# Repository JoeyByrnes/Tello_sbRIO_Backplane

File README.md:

# Tello_sbRIO_Backplane
Hardware Design Files for Tello sbRIO Backplane. For Connecting 10 BiSS-C encoders and 10 AMC drivers to sbRIO.
<br>
<br>
Note: This PCB was not used. I designed this before joining RoboDesign Lab. After joining, I changed the Tello electronics to use a linux computer and MIT mini-cheetah style drivers instead of the sbRIO and AMC drivers.
<br>
<br>
<p>
  
  <br>&nbsp;<br>
  
</p>

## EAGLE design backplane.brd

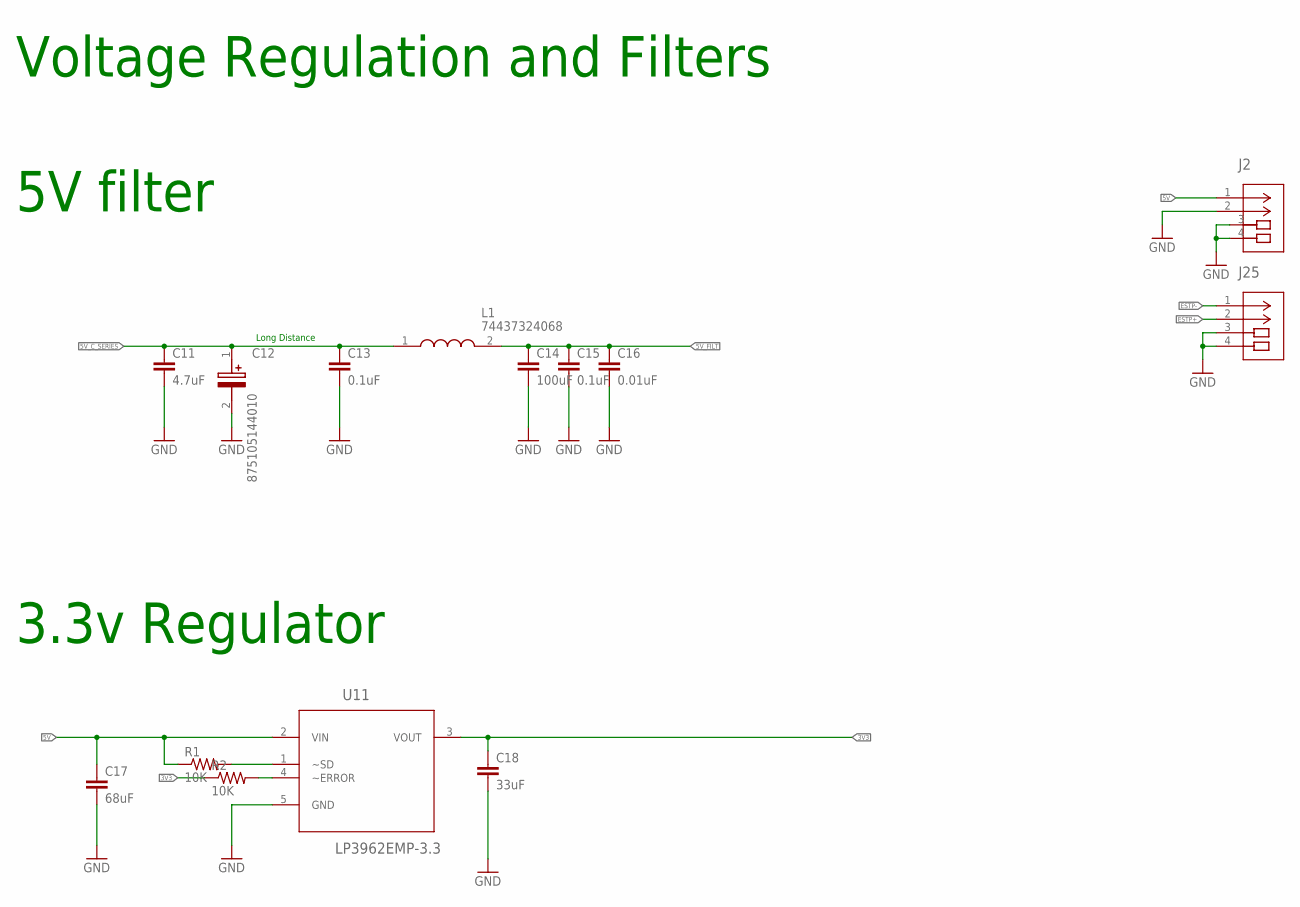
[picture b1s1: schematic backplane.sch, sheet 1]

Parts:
C11: 4.7uF; C0603
C12: 875105144010; CAPAE660X580N
C13, C15: 0.1uF; C0603
C14: 100uF; C1206
C16: 0.01uF; C0603
C17: 68uF; C1206
C18: 33uF; C1206
J2: 1054301102; CON_1054301102_MOL
J25: 5055670271; CON_5055670271
L1: 74437324068; WE-LHMI_402048
R1, R2: 10K; R0603
U11: LP3962EMP-3.3; SOT150P696X180-5N

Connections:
3V3: C18.1, R2.1, U11.3 (VOUT); also elsewhere on the board
5V: C17.1, J2.1, R1.1, U11.2 (VIN); also elsewhere on the board
5V_C_SERIES: C11.1, C12.1 (+), C13.1, L1.1; also elsewhere on the board
5V_FILT: C14.1, C15.1, C16.1, L1.2; also elsewhere on the board
ESTP+: J25.2; also elsewhere on the board
ESTP-: J25.1; also elsewhere on the board
GND: C11.2, C12.2 (-), C13.2, C14.2, C15.2, C16.2, C17.2, C18.2, J2.2, J2.3, J2.4, J25.3, J25.4, U11.5 (GND); also elsewhere on the board
unnamed: R1.2, U11.1 (~SD)
unnamed: R2.2, U11.4 (~ERROR)

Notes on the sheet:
Voltage Regulation and Filters
5V filter
3.3v Regulator
Long Distance

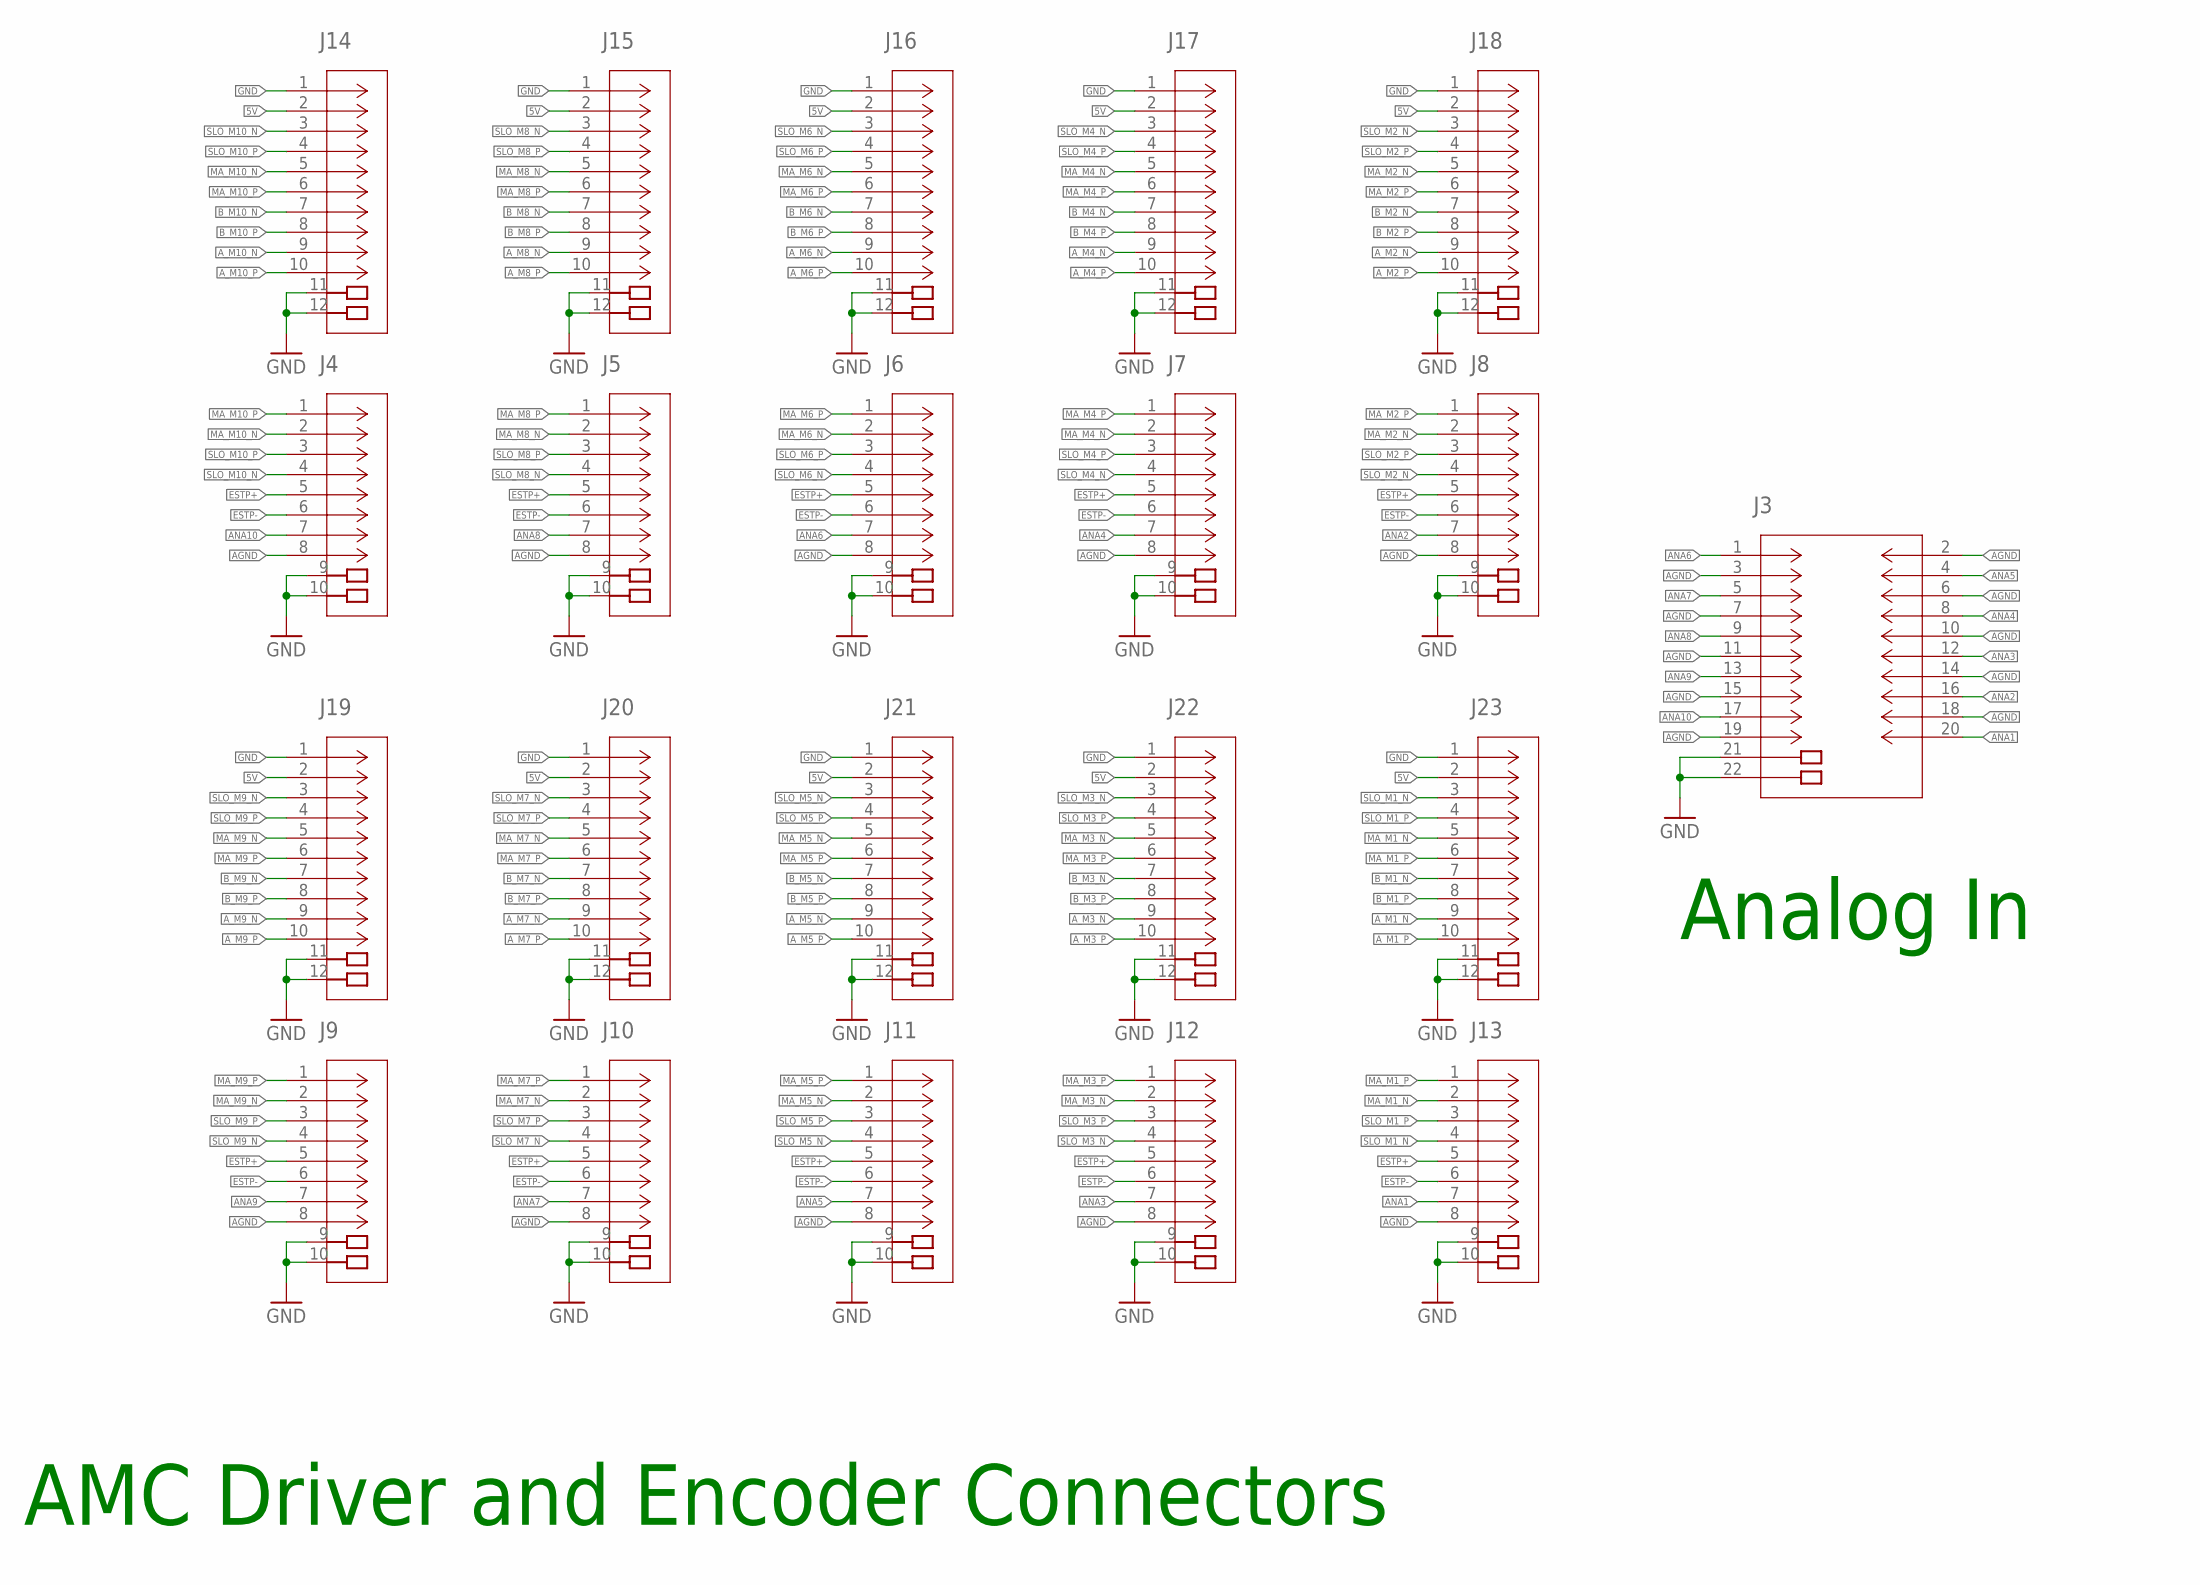
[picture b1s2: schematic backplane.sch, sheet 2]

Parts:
J3: 5011902017; CON_5011902017
J4, J5, J6, J7, J8, J9, J10, J11, J12, J13: 5013310807; CON_5013310807
J14, J15, J16, J17, J18, J19, J20, J21, J22, J23: 5013311007; CON_5013311007

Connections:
5V: J14.2, J15.2, J16.2, J17.2, J18.2, J19.2, J20.2, J21.2, J22.2, J23.2; also elsewhere on the board
AGND: J3.2, J3.3, J3.6, J3.7, J3.10, J3.11, J3.14, J3.15, J3.18, J3.19, J4.8, J5.8, J6.8, J7.8, J8.8, J9.8, J10.8, J11.8, J12.8, J13.8
ANA1: J3.20, J13.7
ANA2: J3.16, J8.7
ANA3: J3.12, J12.7
ANA4: J3.8, J7.7
ANA5: J3.4, J11.7
ANA6: J3.1, J6.7
ANA7: J3.5, J10.7
ANA8: J3.9, J5.7
ANA9: J3.13, J9.7
ANA10: J3.17, J4.7
A_M1_N: J23.9; also elsewhere on the board
A_M1_P: J23.10; also elsewhere on the board
A_M2_N: J18.9; also elsewhere on the board
A_M2_P: J18.10; also elsewhere on the board
A_M3_N: J22.9; also elsewhere on the board
A_M3_P: J22.10; also elsewhere on the board
A_M4_N: J17.9; also elsewhere on the board
A_M4_P: J17.10; also elsewhere on the board
A_M5_N: J21.9; also elsewhere on the board
A_M5_P: J21.10; also elsewhere on the board
A_M6_N: J16.9; also elsewhere on the board
A_M6_P: J16.10; also elsewhere on the board
A_M7_N: J20.9; also elsewhere on the board
A_M7_P: J20.10; also elsewhere on the board
A_M8_N: J15.9; also elsewhere on the board
A_M8_P: J15.10; also elsewhere on the board
A_M9_N: J19.9; also elsewhere on the board
A_M9_P: J19.10; also elsewhere on the board
A_M10_N: J14.9; also elsewhere on the board
A_M10_P: J14.10; also elsewhere on the board
B_M1_N: J23.7; also elsewhere on the board
B_M1_P: J23.8; also elsewhere on the board
B_M2_N: J18.7; also elsewhere on the board
B_M2_P: J18.8; also elsewhere on the board
B_M3_N: J22.7; also elsewhere on the board
B_M3_P: J22.8; also elsewhere on the board
B_M4_N: J17.7; also elsewhere on the board
B_M4_P: J17.8; also elsewhere on the board
B_M5_N: J21.7; also elsewhere on the board
B_M5_P: J21.8; also elsewhere on the board
B_M6_N: J16.7; also elsewhere on the board
B_M6_P: J16.8; also elsewhere on the board
B_M7_N: J20.7; also elsewhere on the board
B_M7_P: J20.8; also elsewhere on the board
B_M8_N: J15.7; also elsewhere on the board
B_M8_P: J15.8; also elsewhere on the board
B_M9_N: J19.7; also elsewhere on the board
B_M9_P: J19.8; also elsewhere on the board
B_M10_N: J14.7; also elsewhere on the board
B_M10_P: J14.8; also elsewhere on the board
ESTP+: J4.5, J5.5, J6.5, J7.5, J8.5, J9.5, J10.5, J11.5, J12.5, J13.5; also elsewhere on the board
ESTP-: J4.6, J5.6, J6.6, J7.6, J8.6, J9.6, J10.6, J11.6, J12.6, J13.6; also elsewhere on the board
GND: J3.21, J3.22, J4.9, J4.10, J5.9, J5.10, J6.9, J6.10, J7.9, J7.10, J8.9, J8.10, J9.9, J9.10, J10.9, J10.10, J11.9, J11.10, J12.9, J12.10, J13.9, J13.10, J14.1, J14.11, J14.12, J15.1, J15.11, J15.12, J16.1, J16.11, J16.12, J17.1, J17.11, J17.12, J18.1, J18.11, J18.12, J19.1, J19.11, J19.12, J20.1, J20.11, J20.12, J21.1, J21.11, J21.12, J22.1, J22.11, J22.12, J23.1, J23.11, J23.12; also elsewhere on the board
MA_M1_N: J13.2, J23.5; also elsewhere on the board
MA_M1_P: J13.1, J23.6; also elsewhere on the board
MA_M2_N: J8.2, J18.5; also elsewhere on the board
MA_M2_P: J8.1, J18.6; also elsewhere on the board
MA_M3_N: J12.2, J22.5; also elsewhere on the board
MA_M3_P: J12.1, J22.6; also elsewhere on the board
MA_M4_N: J7.2, J17.5; also elsewhere on the board
MA_M4_P: J7.1, J17.6; also elsewhere on the board
MA_M5_N: J11.2, J21.5; also elsewhere on the board
MA_M5_P: J11.1, J21.6; also elsewhere on the board
MA_M6_N: J6.2, J16.5; also elsewhere on the board
MA_M6_P: J6.1, J16.6; also elsewhere on the board
MA_M7_N: J10.2, J20.5; also elsewhere on the board
MA_M7_P: J10.1, J20.6; also elsewhere on the board
MA_M8_N: J5.2, J15.5; also elsewhere on the board
MA_M8_P: J5.1, J15.6; also elsewhere on the board
MA_M9_N: J9.2, J19.5; also elsewhere on the board
MA_M9_P: J9.1, J19.6; also elsewhere on the board
MA_M10_N: J4.2, J14.5; also elsewhere on the board
MA_M10_P: J4.1, J14.6; also elsewhere on the board
SLO_M1_N: J13.4, J23.3; also elsewhere on the board
SLO_M1_P: J13.3, J23.4; also elsewhere on the board
SLO_M2_N: J8.4, J18.3; also elsewhere on the board
SLO_M2_P: J8.3, J18.4; also elsewhere on the board
SLO_M3_N: J12.4, J22.3; also elsewhere on the board
SLO_M3_P: J12.3, J22.4; also elsewhere on the board
SLO_M4_N: J7.4, J17.3; also elsewhere on the board
SLO_M4_P: J7.3, J17.4; also elsewhere on the board
SLO_M5_N: J11.4, J21.3; also elsewhere on the board
SLO_M5_P: J11.3, J21.4; also elsewhere on the board
SLO_M6_N: J6.4, J16.3; also elsewhere on the board
SLO_M6_P: J6.3, J16.4; also elsewhere on the board
SLO_M7_N: J10.4, J20.3; also elsewhere on the board
SLO_M7_P: J10.3, J20.4; also elsewhere on the board
SLO_M8_N: J5.4, J15.3; also elsewhere on the board
SLO_M8_P: J5.3, J15.4; also elsewhere on the board
SLO_M9_N: J9.4, J19.3; also elsewhere on the board
SLO_M9_P: J9.3, J19.4; also elsewhere on the board
SLO_M10_N: J4.4, J14.3; also elsewhere on the board
SLO_M10_P: J4.3, J14.4; also elsewhere on the board

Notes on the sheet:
AMC Driver and Encoder Connectors
Analog In

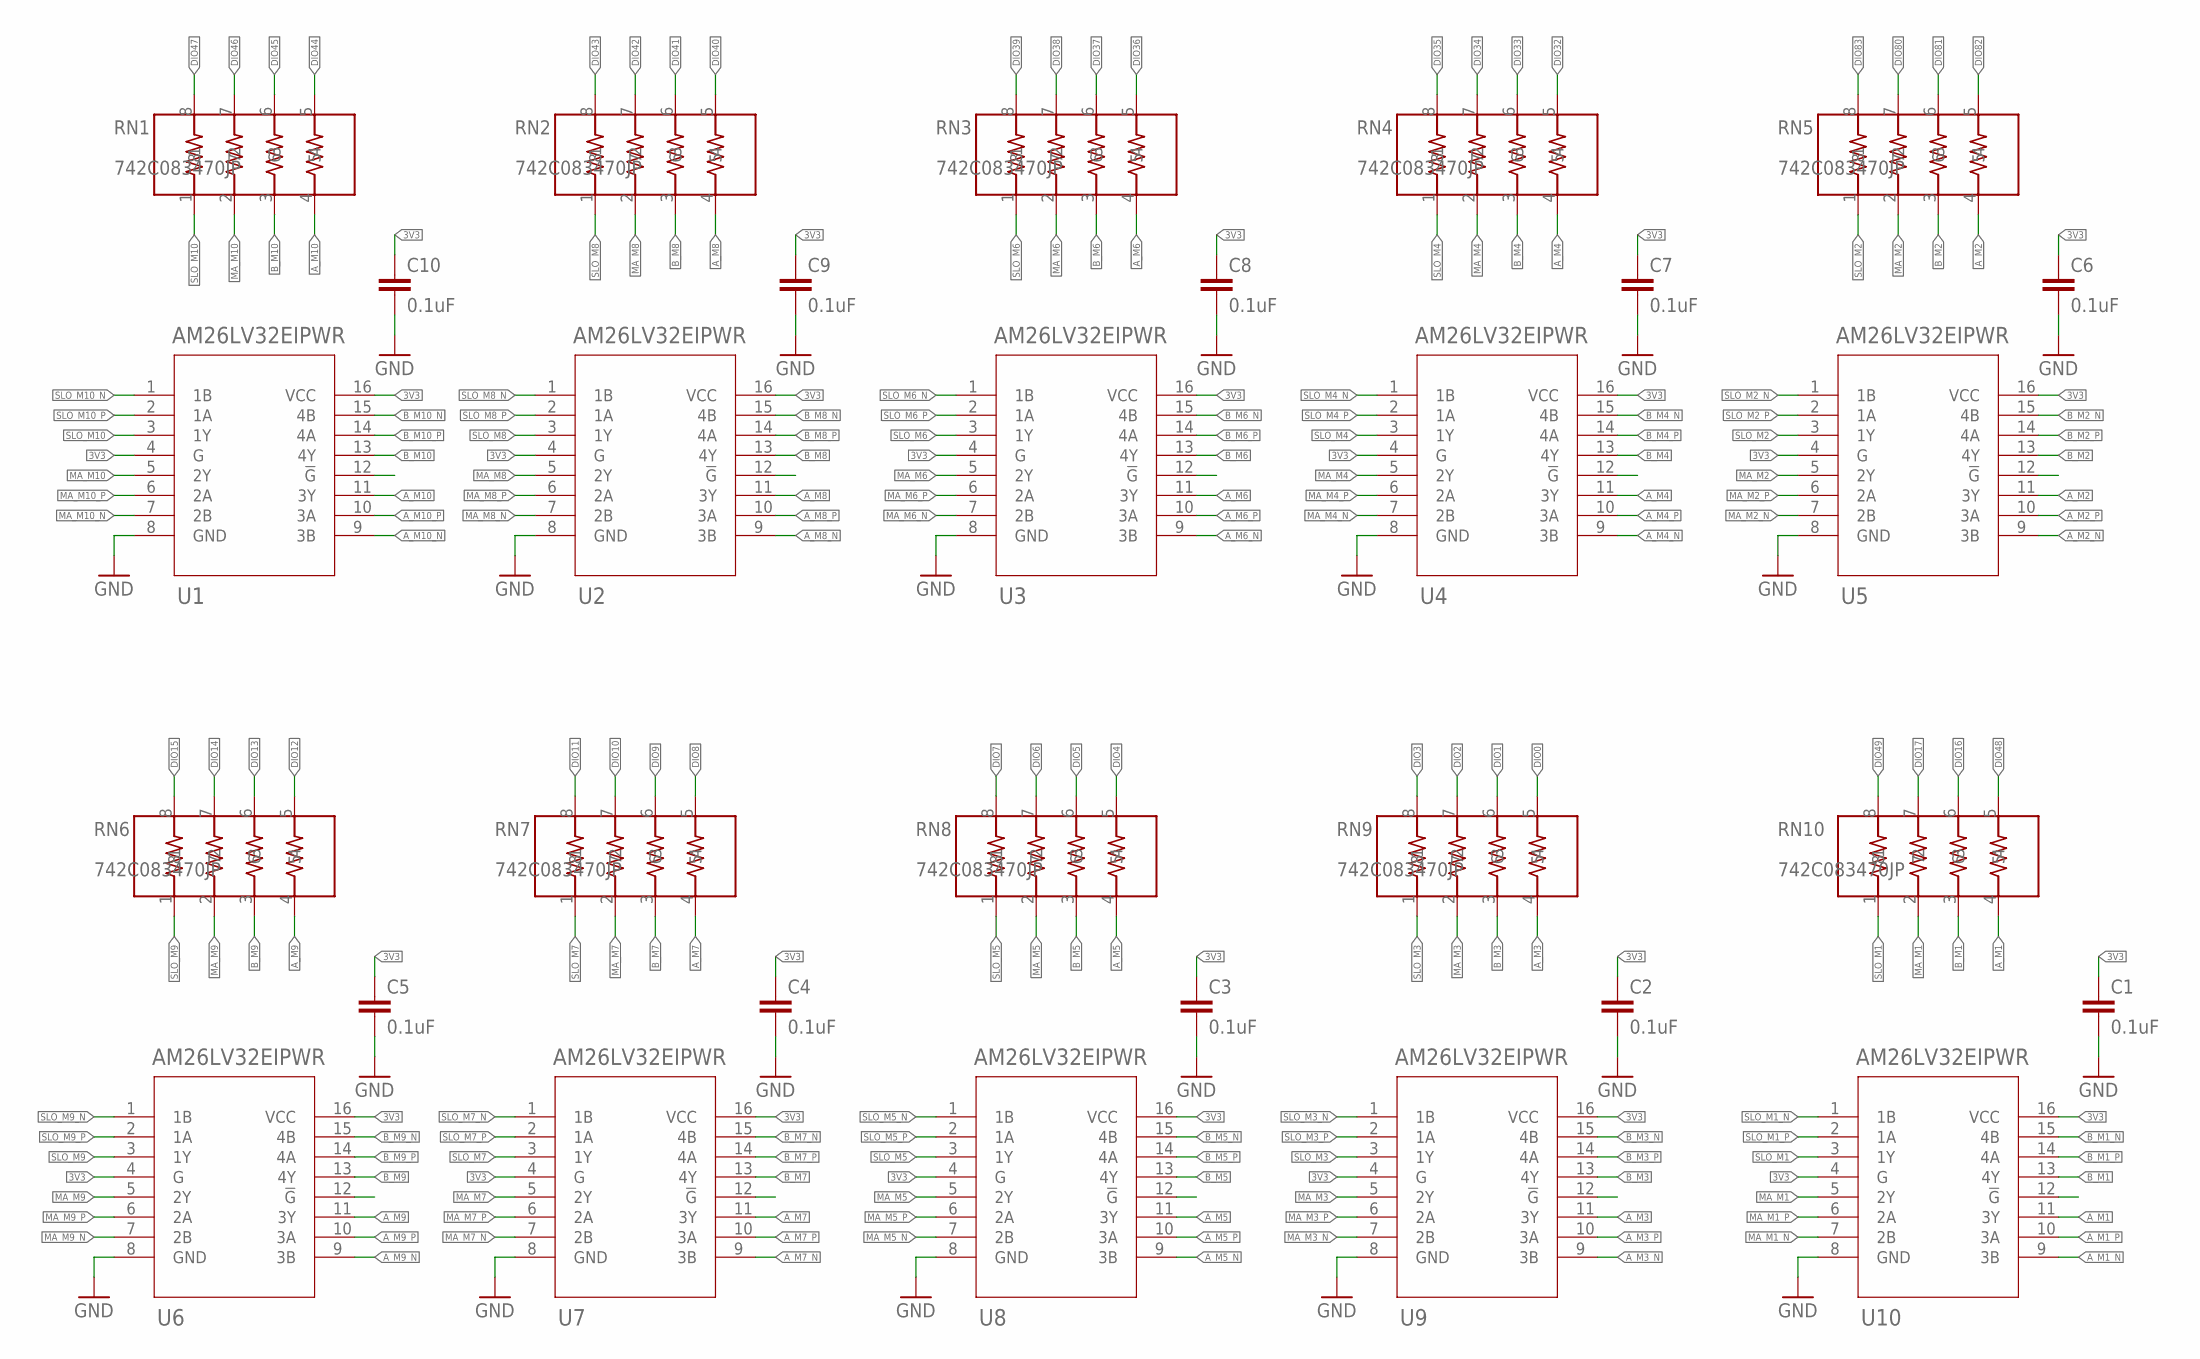
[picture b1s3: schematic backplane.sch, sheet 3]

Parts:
C1, C2, C3, C4, C5, C6, C7, C8, C9, C10: 0.1uF; C0603
RN1, RN2, RN3, RN4, RN5, RN6, RN7, RN8, RN9, RN10: 742C083470JP; RESCAV80P320X160X70-8N
U1, U2, U3, U4, U5, U6, U7, U8, U9, U10: AM26LV32EIPWR; PW16

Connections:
3V3: C1.1, C2.1, C3.1, C4.1, C5.1, C6.1, C7.1, C8.1, C9.1, C10.1, U1.4 (G), U1.16 (VCC), U2.4 (G), U2.16 (VCC), U3.4 (G), U3.16 (VCC), U4.4 (G), U4.16 (VCC), U5.4 (G), U5.16 (VCC), U6.4 (G), U6.16 (VCC), U7.4 (G), U7.16 (VCC), U8.4 (G), U8.16 (VCC), U9.4 (G), U9.16 (VCC), U10.4 (G), U10.16 (VCC); also elsewhere on the board
A_M1: RN10.4, U10.11 (3Y)
A_M1_N: U10.9 (3B); also elsewhere on the board
A_M1_P: U10.10 (3A); also elsewhere on the board
A_M2: RN5.4, U5.11 (3Y)
A_M2_N: U5.9 (3B); also elsewhere on the board
A_M2_P: U5.10 (3A); also elsewhere on the board
A_M3: RN9.4, U9.11 (3Y)
A_M3_N: U9.9 (3B); also elsewhere on the board
A_M3_P: U9.10 (3A); also elsewhere on the board
A_M4: RN4.4, U4.11 (3Y)
A_M4_N: U4.9 (3B); also elsewhere on the board
A_M4_P: U4.10 (3A); also elsewhere on the board
A_M5: RN8.4, U8.11 (3Y)
A_M5_N: U8.9 (3B); also elsewhere on the board
A_M5_P: U8.10 (3A); also elsewhere on the board
A_M6: RN3.4, U3.11 (3Y)
A_M6_N: U3.9 (3B); also elsewhere on the board
A_M6_P: U3.10 (3A); also elsewhere on the board
A_M7: RN7.4, U7.11 (3Y)
A_M7_N: U7.9 (3B); also elsewhere on the board
A_M7_P: U7.10 (3A); also elsewhere on the board
A_M8: RN2.4, U2.11 (3Y)
A_M8_N: U2.9 (3B); also elsewhere on the board
A_M8_P: U2.10 (3A); also elsewhere on the board
A_M9: RN6.4, U6.11 (3Y)
A_M9_N: U6.9 (3B); also elsewhere on the board
A_M9_P: U6.10 (3A); also elsewhere on the board
A_M10: RN1.4, U1.11 (3Y)
A_M10_N: U1.9 (3B); also elsewhere on the board
A_M10_P: U1.10 (3A); also elsewhere on the board
B_M1: RN10.3, U10.13 (4Y)
B_M1_N: U10.15 (4B); also elsewhere on the board
B_M1_P: U10.14 (4A); also elsewhere on the board
B_M2: RN5.3, U5.13 (4Y)
B_M2_N: U5.15 (4B); also elsewhere on the board
B_M2_P: U5.14 (4A); also elsewhere on the board
B_M3: RN9.3, U9.13 (4Y)
B_M3_N: U9.15 (4B); also elsewhere on the board
B_M3_P: U9.14 (4A); also elsewhere on the board
B_M4: RN4.3, U4.13 (4Y)
B_M4_N: U4.15 (4B); also elsewhere on the board
B_M4_P: U4.14 (4A); also elsewhere on the board
B_M5: RN8.3, U8.13 (4Y)
B_M5_N: U8.15 (4B); also elsewhere on the board
B_M5_P: U8.14 (4A); also elsewhere on the board
B_M6: RN3.3, U3.13 (4Y)
B_M6_N: U3.15 (4B); also elsewhere on the board
B_M6_P: U3.14 (4A); also elsewhere on the board
B_M7: RN7.3, U7.13 (4Y)
B_M7_N: U7.15 (4B); also elsewhere on the board
B_M7_P: U7.14 (4A); also elsewhere on the board
B_M8: RN2.3, U2.13 (4Y)
B_M8_N: U2.15 (4B); also elsewhere on the board
B_M8_P: U2.14 (4A); also elsewhere on the board
B_M9: RN6.3, U6.13 (4Y)
B_M9_N: U6.15 (4B); also elsewhere on the board
B_M9_P: U6.14 (4A); also elsewhere on the board
B_M10: RN1.3, U1.13 (4Y)
B_M10_N: U1.15 (4B); also elsewhere on the board
B_M10_P: U1.14 (4A); also elsewhere on the board
DIO0: RN9.5; also elsewhere on the board
DIO1: RN9.6; also elsewhere on the board
DIO2: RN9.7; also elsewhere on the board
DIO3: RN9.8; also elsewhere on the board
DIO4: RN8.5; also elsewhere on the board
DIO5: RN8.6; also elsewhere on the board
DIO6: RN8.7; also elsewhere on the board
DIO7: RN8.8; also elsewhere on the board
DIO8: RN7.5; also elsewhere on the board
DIO9: RN7.6; also elsewhere on the board
DIO10: RN7.7; also elsewhere on the board
DIO11: RN7.8; also elsewhere on the board
DIO12: RN6.5; also elsewhere on the board
DIO13: RN6.6; also elsewhere on the board
DIO14: RN6.7; also elsewhere on the board
DIO15: RN6.8; also elsewhere on the board
DIO16: RN10.6; also elsewhere on the board
DIO17: RN10.7; also elsewhere on the board
DIO32: RN4.5; also elsewhere on the board
DIO33: RN4.6; also elsewhere on the board
DIO34: RN4.7; also elsewhere on the board
DIO35: RN4.8; also elsewhere on the board
DIO36: RN3.5; also elsewhere on the board
DIO37: RN3.6; also elsewhere on the board
DIO38: RN3.7; also elsewhere on the board
DIO39: RN3.8; also elsewhere on the board
DIO40: RN2.5; also elsewhere on the board
DIO41: RN2.6; also elsewhere on the board
DIO42: RN2.7; also elsewhere on the board
DIO43: RN2.8; also elsewhere on the board
DIO44: RN1.5; also elsewhere on the board
DIO45: RN1.6; also elsewhere on the board
DIO46: RN1.7; also elsewhere on the board
DIO47: RN1.8; also elsewhere on the board
DIO48: RN10.5; also elsewhere on the board
DIO49: RN10.8; also elsewhere on the board
DIO80: RN5.7; also elsewhere on the board
DIO81: RN5.6; also elsewhere on the board
DIO82: RN5.5; also elsewhere on the board
DIO83: RN5.8; also elsewhere on the board
GND: C1.2, C2.2, C3.2, C4.2, C5.2, C6.2, C7.2, C8.2, C9.2, C10.2, U1.8 (GND), U2.8 (GND), U3.8 (GND), U4.8 (GND), U5.8 (GND), U6.8 (GND), U7.8 (GND), U8.8 (GND), U9.8 (GND), U10.8 (GND); also elsewhere on the board
MA_M1: RN10.2, U10.5 (2Y)
MA_M1_N: U10.7 (2B); also elsewhere on the board
MA_M1_P: U10.6 (2A); also elsewhere on the board
MA_M2: RN5.2, U5.5 (2Y)
MA_M2_N: U5.7 (2B); also elsewhere on the board
MA_M2_P: U5.6 (2A); also elsewhere on the board
MA_M3: RN9.2, U9.5 (2Y)
MA_M3_N: U9.7 (2B); also elsewhere on the board
MA_M3_P: U9.6 (2A); also elsewhere on the board
MA_M4: RN4.2, U4.5 (2Y)
MA_M4_N: U4.7 (2B); also elsewhere on the board
MA_M4_P: U4.6 (2A); also elsewhere on the board
MA_M5: RN8.2, U8.5 (2Y)
MA_M5_N: U8.7 (2B); also elsewhere on the board
MA_M5_P: U8.6 (2A); also elsewhere on the board
MA_M6: RN3.2, U3.5 (2Y)
MA_M6_N: U3.7 (2B); also elsewhere on the board
MA_M6_P: U3.6 (2A); also elsewhere on the board
MA_M7: RN7.2, U7.5 (2Y)
MA_M7_N: U7.7 (2B); also elsewhere on the board
MA_M7_P: U7.6 (2A); also elsewhere on the board
MA_M8: RN2.2, U2.5 (2Y)
MA_M8_N: U2.7 (2B); also elsewhere on the board
MA_M8_P: U2.6 (2A); also elsewhere on the board
MA_M9: RN6.2, U6.5 (2Y)
MA_M9_N: U6.7 (2B); also elsewhere on the board
MA_M9_P: U6.6 (2A); also elsewhere on the board
MA_M10: RN1.2, U1.5 (2Y)
MA_M10_N: U1.7 (2B); also elsewhere on the board
MA_M10_P: U1.6 (2A); also elsewhere on the board
SLO_M1: RN10.1, U10.3 (1Y)
SLO_M1_N: U10.1 (1B); also elsewhere on the board
SLO_M1_P: U10.2 (1A); also elsewhere on the board
SLO_M2: RN5.1, U5.3 (1Y)
SLO_M2_N: U5.1 (1B); also elsewhere on the board
SLO_M2_P: U5.2 (1A); also elsewhere on the board
SLO_M3: RN9.1, U9.3 (1Y)
SLO_M3_N: U9.1 (1B); also elsewhere on the board
SLO_M3_P: U9.2 (1A); also elsewhere on the board
SLO_M4: RN4.1, U4.3 (1Y)
SLO_M4_N: U4.1 (1B); also elsewhere on the board
SLO_M4_P: U4.2 (1A); also elsewhere on the board
SLO_M5: RN8.1, U8.3 (1Y)
SLO_M5_N: U8.1 (1B); also elsewhere on the board
SLO_M5_P: U8.2 (1A); also elsewhere on the board
SLO_M6: RN3.1, U3.3 (1Y)
SLO_M6_N: U3.1 (1B); also elsewhere on the board
SLO_M6_P: U3.2 (1A); also elsewhere on the board
SLO_M7: RN7.1, U7.3 (1Y)
SLO_M7_N: U7.1 (1B); also elsewhere on the board
SLO_M7_P: U7.2 (1A); also elsewhere on the board
SLO_M8: RN2.1, U2.3 (1Y)
SLO_M8_N: U2.1 (1B); also elsewhere on the board
SLO_M8_P: U2.2 (1A); also elsewhere on the board
SLO_M9: RN6.1, U6.3 (1Y)
SLO_M9_N: U6.1 (1B); also elsewhere on the board
SLO_M9_P: U6.2 (1A); also elsewhere on the board
SLO_M10: RN1.1, U1.3 (1Y)
SLO_M10_N: U1.1 (1B); also elsewhere on the board
SLO_M10_P: U1.2 (1A); also elsewhere on the board

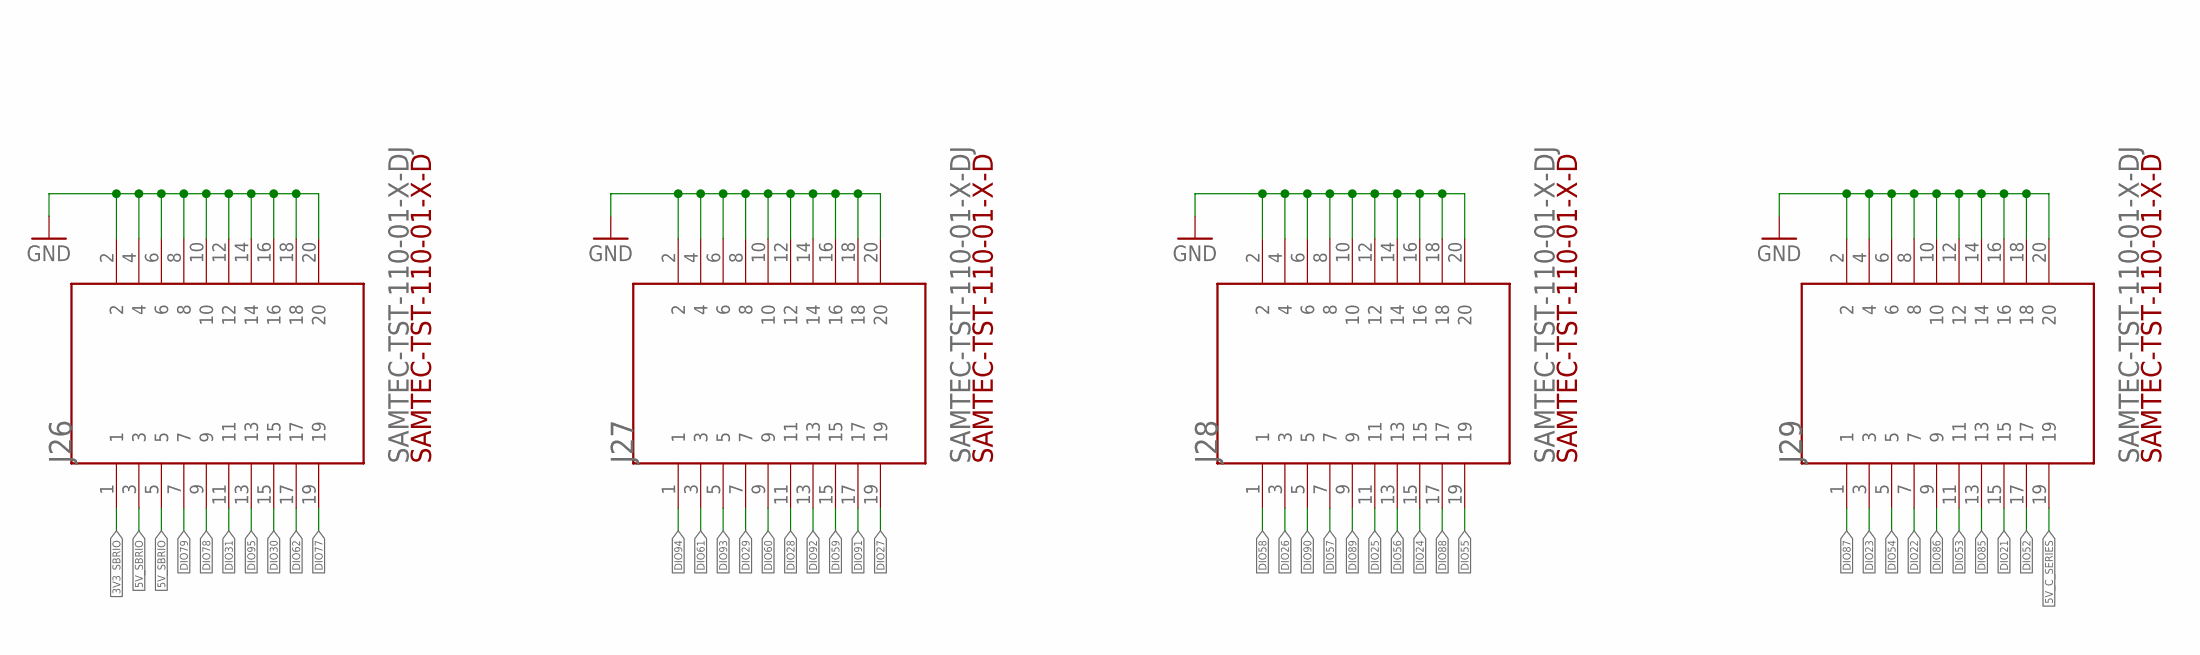
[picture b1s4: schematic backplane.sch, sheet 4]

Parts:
J26, J27, J28, J29: SAMTEC-TST-110-01-X-DJ; SAMTEC-TST-110-01-X-D

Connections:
3V3_SBRIO: J26.1; also elsewhere on the board
5V_C_SERIES: J29.19; also elsewhere on the board
5V_SBRIO: J26.3, J26.5; also elsewhere on the board
DIO21: J29.15; also elsewhere on the board
DIO22: J29.7; also elsewhere on the board
DIO23: J29.3; also elsewhere on the board
DIO24: J28.15; also elsewhere on the board
DIO25: J28.11; also elsewhere on the board
DIO26: J28.3; also elsewhere on the board
DIO27: J27.19; also elsewhere on the board
DIO28: J27.11; also elsewhere on the board
DIO29: J27.7; also elsewhere on the board
DIO30: J26.15; also elsewhere on the board
DIO31: J26.11; also elsewhere on the board
DIO52: J29.17; also elsewhere on the board
DIO53: J29.11; also elsewhere on the board
DIO54: J29.5; also elsewhere on the board
DIO55: J28.19; also elsewhere on the board
DIO56: J28.13; also elsewhere on the board
DIO57: J28.7; also elsewhere on the board
DIO58: J28.1; also elsewhere on the board
DIO59: J27.15; also elsewhere on the board
DIO60: J27.9; also elsewhere on the board
DIO61: J27.3; also elsewhere on the board
DIO62: J26.17; also elsewhere on the board
DIO77: J26.19; also elsewhere on the board
DIO78: J26.9; also elsewhere on the board
DIO79: J26.7; also elsewhere on the board
DIO85: J29.13; also elsewhere on the board
DIO86: J29.9; also elsewhere on the board
DIO87: J29.1; also elsewhere on the board
DIO88: J28.17; also elsewhere on the board
DIO89: J28.9; also elsewhere on the board
DIO90: J28.5; also elsewhere on the board
DIO91: J27.17; also elsewhere on the board
DIO92: J27.13; also elsewhere on the board
DIO93: J27.5; also elsewhere on the board
DIO94: J27.1; also elsewhere on the board
DIO95: J26.13; also elsewhere on the board
GND: J26.2, J26.4, J26.6, J26.8, J26.10, J26.12, J26.14, J26.16, J26.18, J26.20, J27.2, J27.4, J27.6, J27.8, J27.10, J27.12, J27.14, J27.16, J27.18, J27.20, J28.2, J28.4, J28.6, J28.8, J28.10, J28.12, J28.14, J28.16, J28.18, J28.20, J29.2, J29.4, J29.6, J29.8, J29.10, J29.12, J29.14, J29.16, J29.18, J29.20; also elsewhere on the board

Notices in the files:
parts and their libraries:
COPYRIGHT: Copyright (C) 2022 Ultra Librarian. All rights reserved.
